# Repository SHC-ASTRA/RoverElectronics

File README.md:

View this project on [CADLAB.io](https://cadlab.io/project/23863). 

# RoverElectronics
Electronics hardware for the full-scale rover

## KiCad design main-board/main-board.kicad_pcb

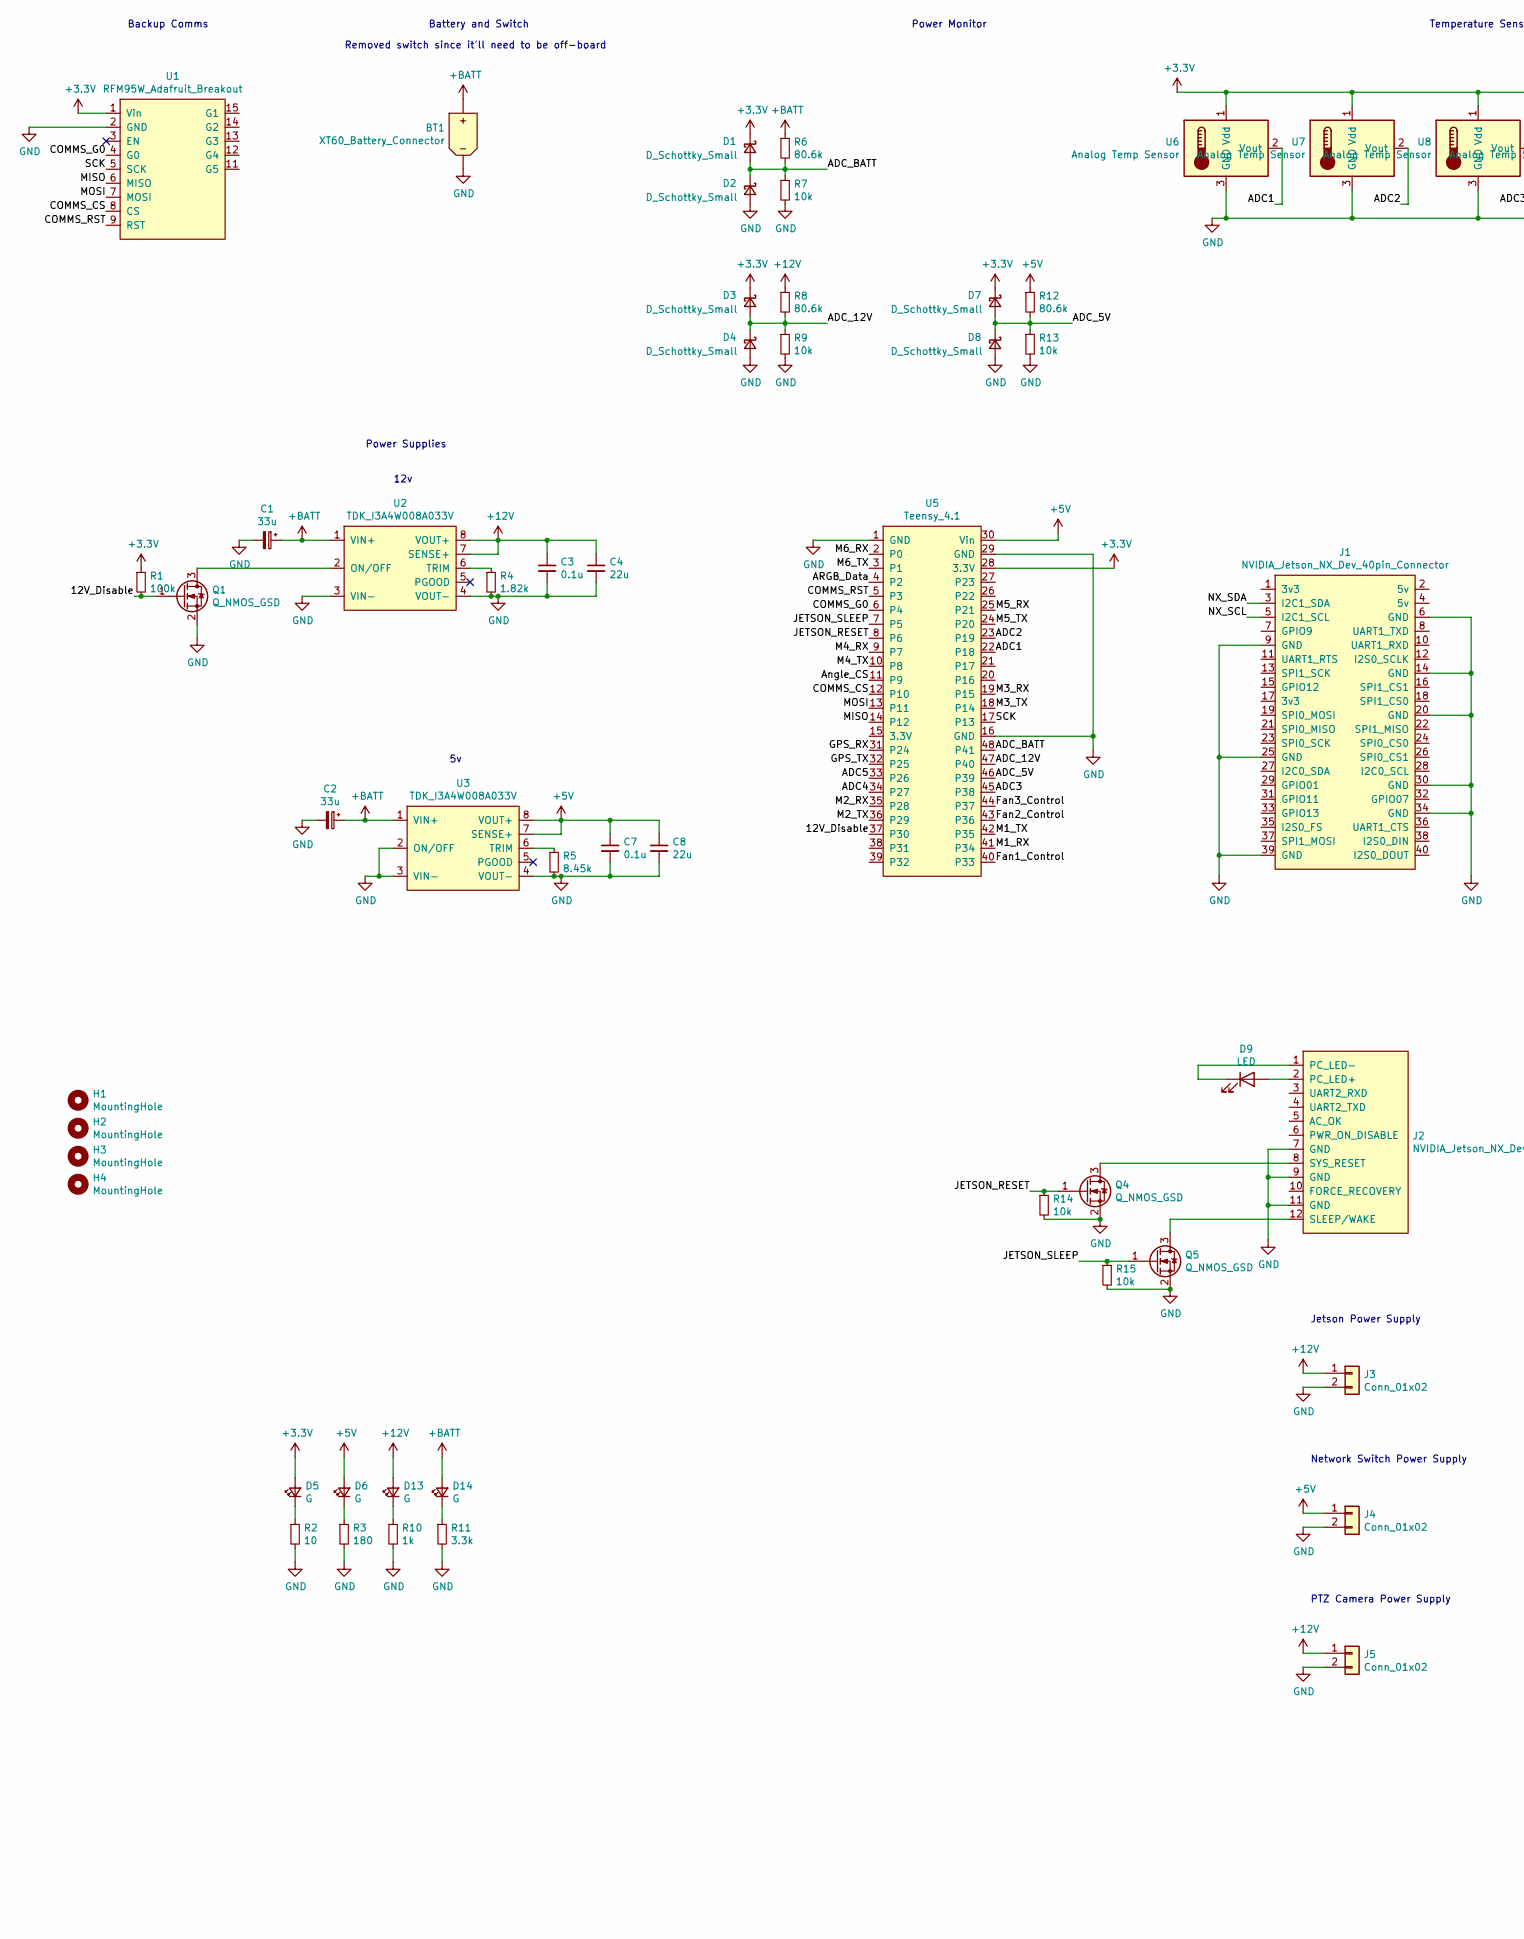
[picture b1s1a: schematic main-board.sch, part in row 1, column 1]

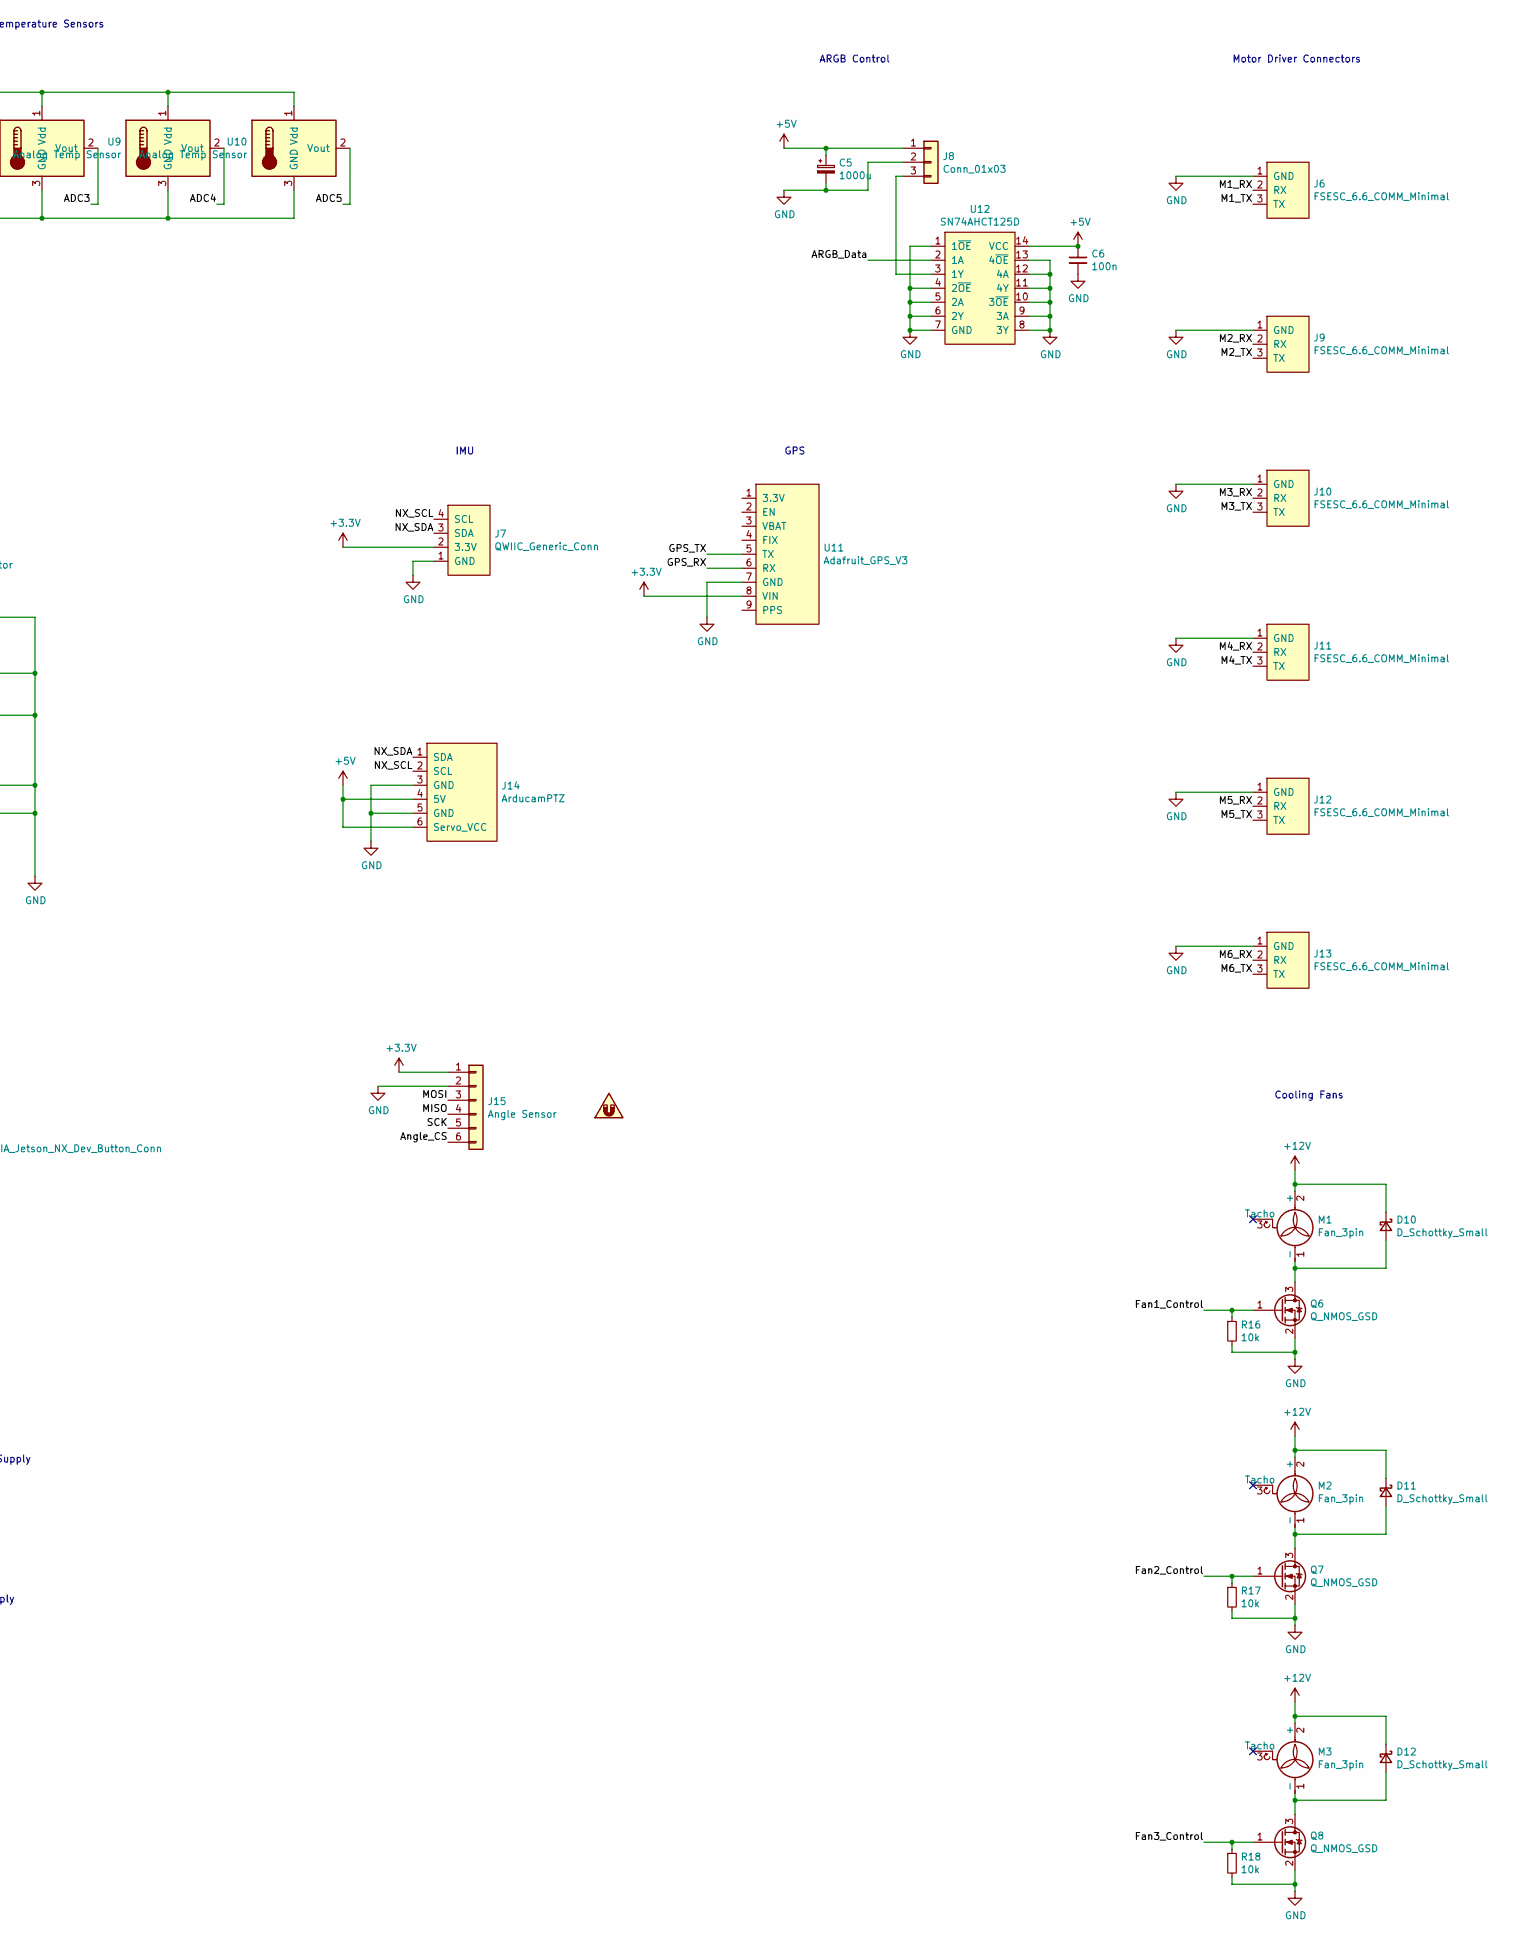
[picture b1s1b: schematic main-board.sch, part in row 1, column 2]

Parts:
BT1: XT60_Battery_Connector; AMASS_XT60-M_1x02_P7.20mm_Vertical
C1, C2: 33u; CP_Elec_8x5.4; Digikey Part Num 493-2137-1-ND
C3, C7: 0.1u; C_0603_1608Metric
C4, C8: 22u; C_1210_3225Metric; Digikey Part Num 311-2053-1-ND
C5: 1000u; CP_Radial_D8.0mm_P3.50mm; Digikey Part Num 493-10756-1-ND
C6: 100n; C_0603_1608Metric; Digikey Part Num 1276-1941-1-ND
D1, D2, D3, D4, D7, D8: D_Schottky_Small; D_SOD-323_HandSoldering; Digikey Part Num 1514-CMDD6001TRPBFREECT-ND
D5, D6, D13, D14: G; LED_0603_1608Metric_Pad1.05x0.95mm_HandSolder; Digikey Part Num 732-4971-1-ND
D9: LED; LED_0603_1608Metric_Pad1.05x0.95mm_HandSolder; Digikey Part Num 732-4980-1-ND
D10, D11, D12: D_Schottky_Small; D_SOD-123F; Digikey Part Num 1655-1927-1-ND
H1, H2, H3, H4: MountingHole; MountingHole_3.2mm_M3_Pad
J1: NVIDIA_Jetson_NX_Dev_40pin_Connector; IDC-Header_2x20_P2.54mm_Vertical; Digikey Part Num S9175-ND
J2: NVIDIA_Jetson_NX_Dev_Button_Conn; PinHeader_1x12_P2.54mm_Vertical
J3, J4, J5: Conn_01x02; JST_XH_B2B-XH-A_1x02_P2.50mm_Vertical; Digikey Part Num 455-2247-ND
J6, J9, J10, J11, J12, J13: FSESC_6.6_COMM_Minimal; JST_PH_B3B-PH-K_1x03_P2.00mm_Vertical
J7: QWIIC_Generic_Conn; JST_SH_SM04B-SRSS-TB_1x04-1MP_P1.00mm_Horizontal; Digikey Part Num 455-1804-1-ND
J8: Conn_01x03; JST_PH_B3B-PH-K_1x03_P2.00mm_Vertical; Digikey Part Num ~ JST PH
J14: ArducamPTZ; JST_XH_B6B-XH-A_1x06_P2.50mm_Vertical
J15: Angle Sensor; JST_PH_B6B-PH-K_1x06_P2.00mm_Vertical
M1, M2, M3: Fan_3pin; Molex_KK-254_AE-6410-03A_1x03_P2.54mm_Vertical; Digikey Part Num WM2701-ND
Q1, Q4, Q5, Q6, Q7, Q8: Q_NMOS_GSD; SOT-23; Digikey Part Num SSM3K2615RLFCT-ND
R1: 100k; R_0603_1608Metric; Digikey Part Num 311-100KHRCT-ND
R2: 10; R_0603_1608Metric; Digikey Part Num 311-10.0HRCT-ND
R3: 180; R_0603_1608Metric; Digikey Part Num 311-180HRCT-ND
R4: 1.82k; R_0603_1608Metric; Digikey Part Num 311-1.82KHRCT-ND
R5: 8.45k; R_0603_1608Metric; Digikey Part Num 311-8.45KHRCT-ND
R6, R8, R12: 80.6k; R_0603_1608Metric; Digikey Part Num P20500CT-ND
R7, R9, R13, R14, R15, R16, R17, R18: 10k; R_0603_1608Metric; Digikey Part Num 311-10.0KHRCT-ND
R10: 1k; R_0603_1608Metric; Digikey Part Num 311-1.00KHRCT-ND
R11: 3.3k; R_0603_1608Metric; Digikey Part Num 311-3.30KHRCT-ND
SYM1: SYM_Magnet_Small; Digikey Part Num 469-1025-ND
U1: RFM95W_Adafruit_Breakout; Adafruit_RFM95W; Digikey Part Num 1528-1667-ND
U2, U3: TDK_I3A4W008A033V; Power_Supply_32nd_Brick; Digikey Part Num 285-2720-ND
U5: Teensy_4.1; Teensy4.1; Digikey Part Num 1568-DEV-16771-ND
U6, U7: Analog Temp Sensor; TO-92; Digikey Part Num 296-46127-1-ND
U8, U9, U10: Analog Temp Sensor; JST_PH_B3B-PH-K_1x03_P2.00mm_Vertical; Digikey Part Num 296-46127-1-ND
U11: Adafruit_GPS_V3; Adafruit_GPS_Breakout; Digikey Part Num 1528-1153-ND
U12: SN74AHCT125D; SOIC-14_3.9x8.7mm_P1.27mm; Digikey Part Num 296-4652-5-ND

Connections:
+3V3: D1.1 (K), D3.1 (K), D5.2 (A), D7.1 (K), J7.2 (3.3V), J15.1, R1.1, U1.1 (Vin), U5.28 (3.3V), U6.1 (Vdd), U7.1 (Vdd), U8.1 (Vdd), U9.1 (Vdd), U10.1 (Vdd), U11.8 (VIN)
+5V: C5.1, C6.1, C7.1, C8.1, D6.2 (A), J4.1, J8.1, J14.4 (5V), J14.6 (Servo_VCC), R12.1, U3.7 (SENSE+), U3.8 (VOUT+), U5.30 (Vin), U12.14 (VCC)
+12V: C3.1, C4.1, D10.1 (K), D11.1 (K), D12.1 (K), D13.2 (A), J3.1, J5.1, M1.2 (+), M2.2 (+), M3.2 (+), R8.1, U2.7 (SENSE+), U2.8 (VOUT+)
+BATT: BT1.2 (Pos), C1.1, C2.1, D14.2 (A), R6.1, U2.1 (VIN+), U3.1 (VIN+)
/12V_Disable: Q1.1 (G), R1.2, U5.37 (P30)
/ADC1: U5.22 (P18), U6.2 (Vout)
/ADC2: U5.23 (P19), U7.2 (Vout)
/ADC3: U5.45 (P38), U8.2 (Vout)
/ADC4: U5.34 (P27), U9.2 (Vout)
/ADC5: U5.33 (P26), U10.2 (Vout)
/ADC_5V: D7.2 (A), D8.1 (K), R12.2, R13.1, U5.46 (P39)
/ADC_12V: D3.2 (A), D4.1 (K), R8.2, R9.1, U5.47 (P40)
/ADC_BATT: D1.2 (A), D2.1 (K), R6.2, R7.1, U5.48 (P41)
/ARGB_Data: U5.4 (P2), U12.2 (1A)
/Angle_CS: J15.6, U5.11 (P9)
/COMMS_CS: U1.8 (CS), U5.12 (P10)
/COMMS_G0: U1.4 (G0), U5.6 (P4)
/COMMS_RST: U1.9 (RST), U5.5 (P3)
/Fan1_Control: Q6.1 (G), R16.1, U5.40 (P33)
/Fan2_Control: Q7.1 (G), R17.1, U5.43 (P36)
/Fan3_Control: Q8.1 (G), R18.1, U5.44 (P37)
/GPS_RX: U5.31 (P24), U11.6 (RX)
/GPS_TX: U5.32 (P25), U11.5 (TX)
/JETSON_RESET: Q4.1 (G), R14.1, U5.8 (P6)
/JETSON_SLEEP: Q5.1 (G), R15.1, U5.7 (P5)
/M1_RX: J6.2 (RX), U5.41 (P34)
/M1_TX: J6.3 (TX), U5.42 (P35)
/M2_RX: J9.2 (RX), U5.35 (P28)
/M2_TX: J9.3 (TX), U5.36 (P29)
/M3_RX: J10.2 (RX), U5.19 (P15)
/M3_TX: J10.3 (TX), U5.18 (P14)
/M4_RX: J11.2 (RX), U5.9 (P7)
/M4_TX: J11.3 (TX), U5.10 (P8)
/M5_RX: J12.2 (RX), U5.25 (P21)
/M5_TX: J12.3 (TX), U5.24 (P20)
/M6_RX: J13.2 (RX), U5.2 (P0)
/M6_TX: J13.3 (TX), U5.3 (P1)
/MISO: J15.4, U1.6 (MISO), U5.14 (P12)
/MOSI: J15.3, U1.7 (MOSI), U5.13 (P11)
/NX_SCL: J1.5 (I2C1_SCL), J7.4 (SCL), J14.2 (SCL)
/NX_SDA: J1.3 (I2C1_SDA), J7.3 (SDA), J14.1 (SDA)
/SCK: J15.5, U1.5 (SCK), U5.17 (P13)
GND: BT1.1 (Neg), C1.2, C2.2, C3.2, C4.2, C5.2, C6.2, C7.2, C8.2, D2.2 (A), D4.2 (A), D8.2 (A), J1.6 (GND), J1.9 (GND), J1.14 (GND), J1.20 (GND), J1.25 (GND), J1.30 (GND), J1.34 (GND), J1.39 (GND), J2.7 (GND), J2.9 (GND), J2.11 (GND), J3.2, J4.2, J5.2, J6.1 (GND), J7.1 (GND), J8.2, J9.1 (GND), J10.1 (GND), J11.1 (GND), J12.1 (GND), J13.1 (GND), J14.3 (GND), J14.5 (GND), J15.2, Q1.2 (S), Q4.2 (S), Q5.2 (S), Q6.2 (S), Q7.2 (S), Q8.2 (S), R2.2, R3.2, R4.2, R5.2, R7.2, R9.2, R10.2, R11.2, R13.2, R14.2, R15.2, R16.2, R17.2, R18.2, U1.2 (GND), U2.3 (VIN-), U2.4 (VOUT-), U3.2 (ON/OFF), U3.3 (VIN-), U3.4 (VOUT-), U5.1 (GND), U5.16 (GND), U5.29 (GND), U6.3 (GND), U7.3 (GND), U8.3 (GND), U9.3 (GND), U10.3 (GND), U11.7 (GND), U12.1 (1~OE), U12.4 (2~OE), U12.5 (2A), U12.6 (2Y), U12.7 (GND), U12.8 (3Y), U12.9 (3A), U12.10 (3~OE), U12.11 (4Y), U12.12 (4A), U12.13 (4~OE)
unnamed: D5.1 (K), R2.1
unnamed: D6.1 (K), R3.1
unnamed: D9.1 (K), J2.1 (PC_LED-)
unnamed: D9.2 (A), J2.2 (PC_LED+)
unnamed: D10.2 (A), M1.1 (-), Q6.3 (D)
unnamed: D11.2 (A), M2.1 (-), Q7.3 (D)
unnamed: D12.2 (A), M3.1 (-), Q8.3 (D)
unnamed: D13.1 (K), R10.1
unnamed: D14.1 (K), R11.1
unnamed: J2.8 (SYS_RESET), Q4.3 (D)
unnamed: J2.12 (SLEEP/WAKE), Q5.3 (D)
unnamed: J8.3, U12.3 (1Y)
unnamed: Q1.3 (D), U2.2 (ON/OFF)
unnamed: R4.1, U2.6 (TRIM)
unnamed: R5.1, U3.6 (TRIM)

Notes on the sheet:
Power Supplies
Battery and Switch
Backup Comms
Power Monitor
Temperature Sensors
ARGB Control
Motor Driver Connectors
GPS
IMU
Cooling Fans
Jetson Power Supply
12v
Network Switch Power Supply
Removed switch since it'll need to be off-board
PTZ Camera Power Supply

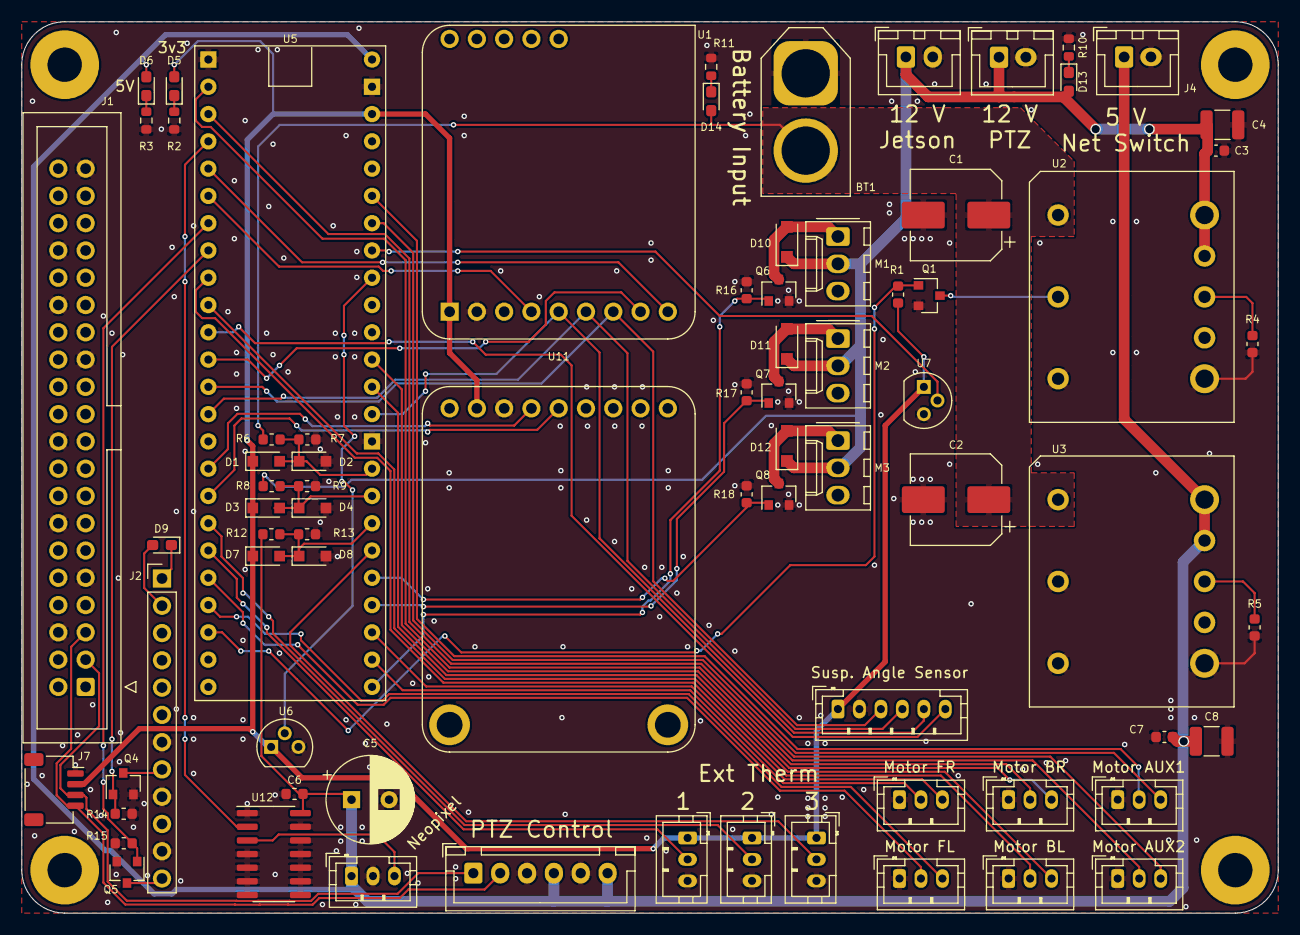
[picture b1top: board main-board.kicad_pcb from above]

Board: 2 copper layers, 117.0 x 83.0 mm, 80 parts (0 on the bottom side), 58 nets.

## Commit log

2021-02-10 Started KiCAD project
2021-02-10 Backlink to CADLAB.io has been added.
2021-04-13 Started filling out schematic
2021-04-13 Added a few more sheets
    Battery
    Jetson power button/LED
    Over-discharge protection
    OpenLog
    Power Supply
2021-04-19 More subsheets
2021-05-27 Subsheets
    Added motor drivers, cooling fans, and openlog
2021-05-27 More subsheets
    Added gps and LED ring
2021-06-12 more subsheets
    backup coms
2021-06-12 Even more subsheets
    switched monitor and temp sensors to ADC. added temp sensors
2021-06-19 Added battery stuff
2021-06-19 added library to main project
2021-06-26 removed battery protection (will be implemented off-board)
2021-07-24 Got rid of hierarchical sheets
2021-07-27 Teensy Connections
    Added the majority of the teensy connections from the excel sheet (minus the coms). Added a few power connections
2021-07-31 changed a few thingies
2021-08-09 small tweaks
2021-08-09 started work on power supplies
2021-08-10 More work on power supply stuff
2021-08-10 Lots of small changes
2021-08-10 started sourcing components
2021-08-11 Parts selected
2021-08-11 Set a lot of footprints
2021-08-11 started PCB
2021-08-12 24v power supply swapped
2021-08-12 pcb layout attempt
    Tried to squish stuff together while still leaving room for traces (probably really rough)
2021-08-12 fixed a small error with footprints
2021-08-12 ahhh i messed some stuff up
2021-08-15 Removed 24V connector, Changed net switch power bus, changed motor driver connector
2021-08-28 Worked on PCB layout
2021-08-28 Started routing
2021-09-04 Shooouuulld be fully routed
2021-09-04 DONE! (hopefully)
2021-09-20 Schematic layout done
2021-09-21 XT60 Fix
2021-09-21 Probably should do a rev increase
2022-03-14 Implemented post SAR fixes
2022-03-15 I changed something?
2022-03-15 something?
2022-03-17 Indicator LEDs
